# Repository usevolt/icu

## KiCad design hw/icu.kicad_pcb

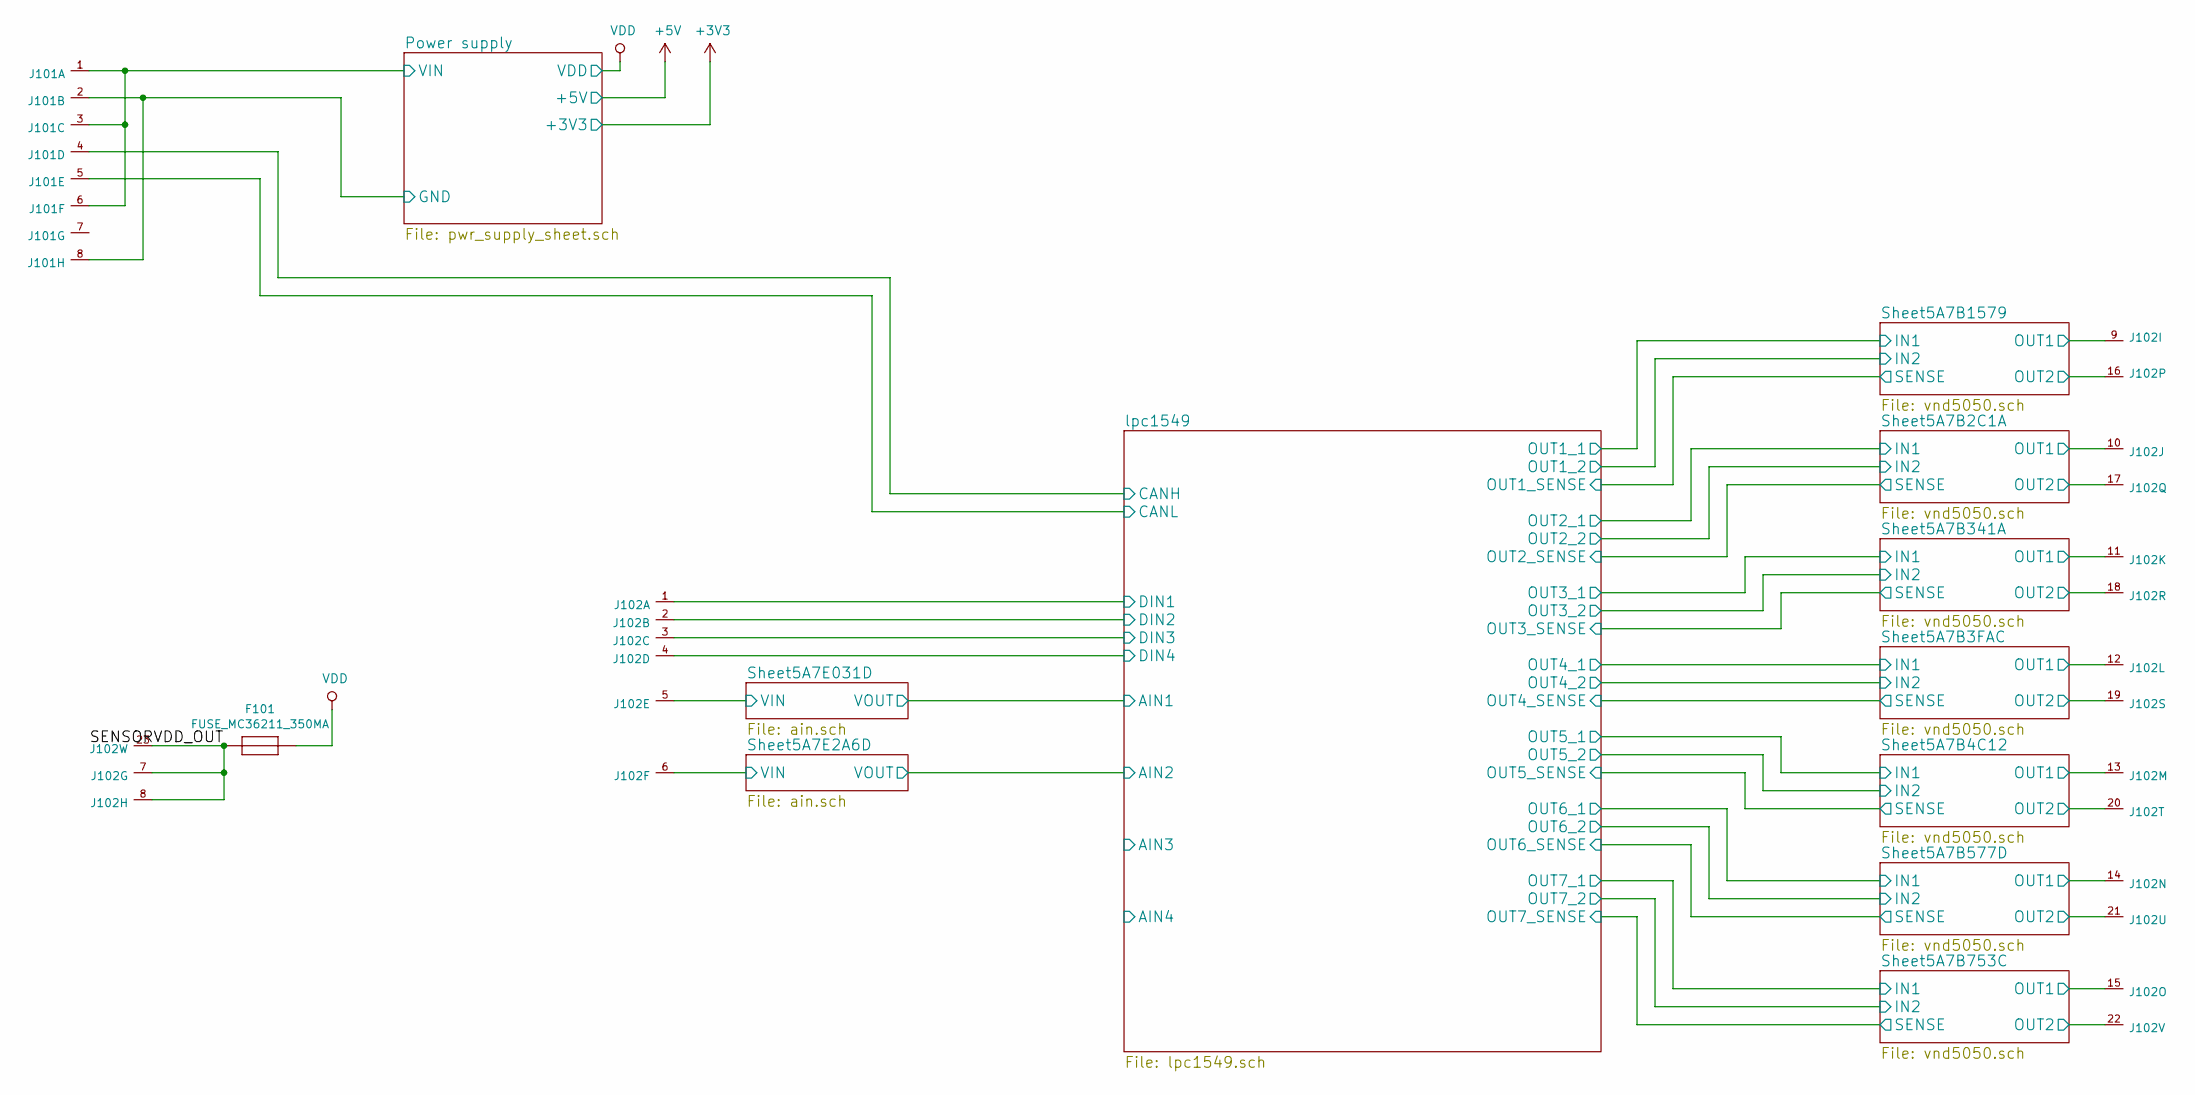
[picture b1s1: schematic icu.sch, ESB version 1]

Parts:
F101: FUSE_MC36211_350MA; FUSE_MC36211; Manufacturer Part Number MC36211
J101: AMPSEAL_8_POS_VERT_BLACK_SEALED_1-776276-1; AMPSEAL_8_POS_776275-1; Manufacturer Part Number 1-776276-1
J102: AMPSEAL_23_POS_VERT_GRAY_SEALED_1-776228-4; AMPSEAL_23_POS_776200-1; Manufacturer Part Number 1-776228-4

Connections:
/Power supply/VIN: J101.1, J101.3, J101.6; also elsewhere on the board
/SENSORVDD_OUT: F101.P$2, J102.7, J102.8, J102.23
/Sheet5A7B2C1A/OUT1: J102.10; also elsewhere on the board
/Sheet5A7B2C1A/OUT2: J102.17; also elsewhere on the board
/Sheet5A7B3FAC/OUT1: J102.12; also elsewhere on the board
/Sheet5A7B3FAC/OUT2: J102.19; also elsewhere on the board
/Sheet5A7B4C12/OUT1: J102.13; also elsewhere on the board
/Sheet5A7B4C12/OUT2: J102.20; also elsewhere on the board
/Sheet5A7B341A/OUT1: J102.11; also elsewhere on the board
/Sheet5A7B341A/OUT2: J102.18; also elsewhere on the board
/Sheet5A7B577D/OUT1: J102.14; also elsewhere on the board
/Sheet5A7B577D/OUT2: J102.21; also elsewhere on the board
/Sheet5A7B753C/OUT1: J102.15; also elsewhere on the board
/Sheet5A7B753C/OUT2: J102.22; also elsewhere on the board
/Sheet5A7B1579/OUT1: J102.9; also elsewhere on the board
/Sheet5A7B1579/OUT2: J102.16; also elsewhere on the board
/Sheet5A7E2A6D/VIN: J102.6; also elsewhere on the board
/Sheet5A7E031D/VIN: J102.5; also elsewhere on the board
/lpc1549/CANH: J101.4; also elsewhere on the board
/lpc1549/CANL: J101.5; also elsewhere on the board
/lpc1549/DIN1: J102.1; also elsewhere on the board
/lpc1549/DIN2: J102.2; also elsewhere on the board
/lpc1549/DIN3: J102.3; also elsewhere on the board
/lpc1549/DIN4: J102.4; also elsewhere on the board
GND: J101.2, J101.8; also elsewhere on the board
VDD: F101.P$1; also elsewhere on the board

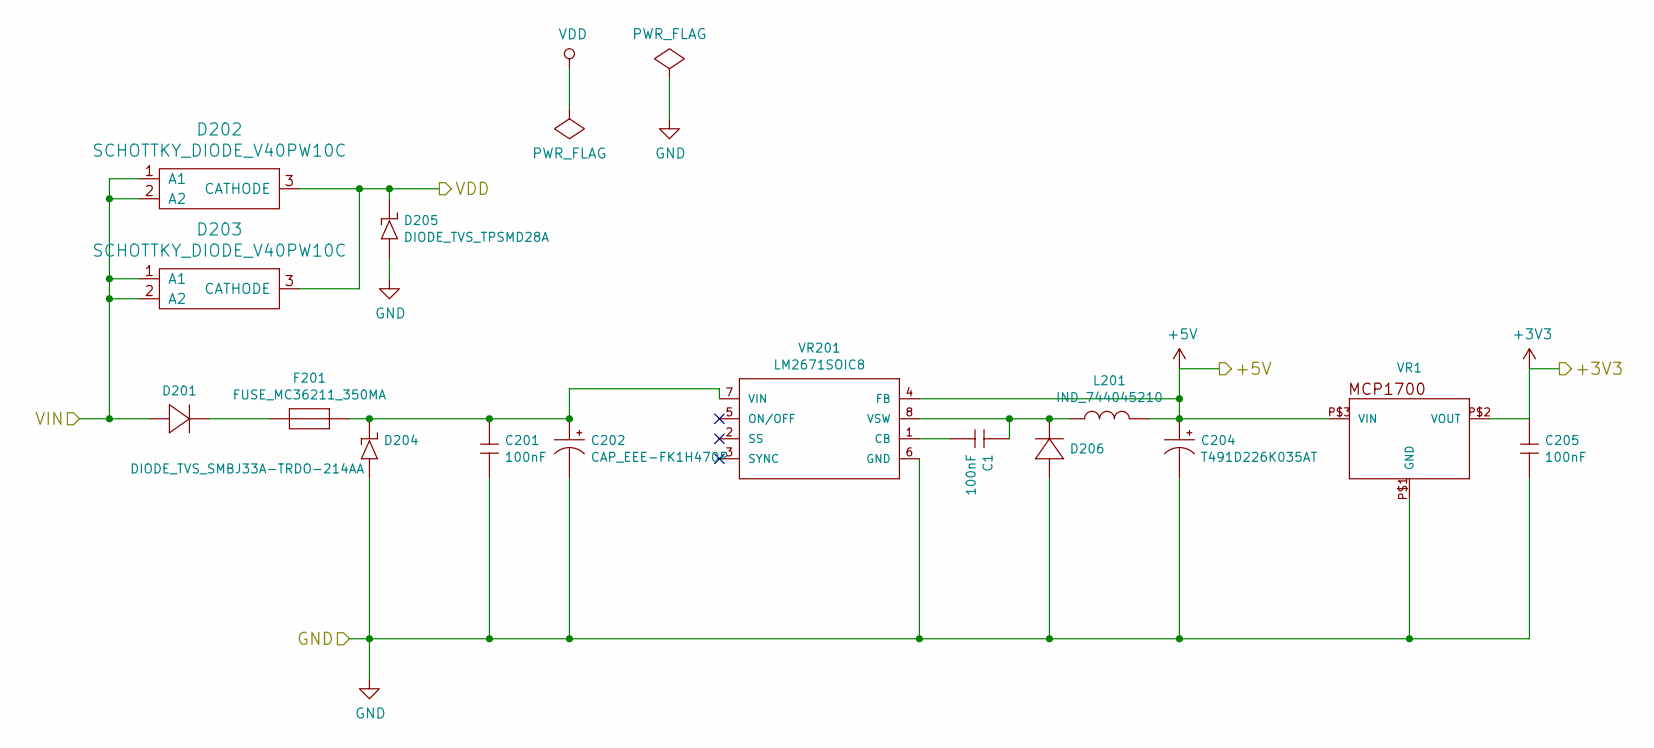
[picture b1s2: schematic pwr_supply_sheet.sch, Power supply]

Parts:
C1, C201, C205: 100nF; 0603; Manufacturer Part Number C0603C104K5RACTU
C202: CAP_EEE-FK1H470P; Manufacturer Part Number EEE-FK1H470P
C204: T491D226K035AT; 7343; Manufacturer Part Number T491D226K035AT
D201, D206: DIODE_RS07J-GS18; DO219AB; Manufacturer Part Number RS07J-GS18
D202, D203: SCHOTTKY_DIODE_V40PW10C; SlimDPAK; Manufacturer Part Number V40PW10CHM3/I
D204: DIODE_TVS_SMBJ33A-TRDO-214AA; DO-214AA; Manufacturer Part Number SMBJ33A
D205: DIODE_TVS_TPSMD28A; DO-214AB; Manufacturer Part Number TPSMD28A
F201: FUSE_MC36211_350MA; FUSE_MC36211; Manufacturer Part Number MC36211
L201: IND_744045210; Manufacturer Part Number 744045210
VR1: REG_MCP1700; SOT-23_3-PIN; Manufacturer Part Number MCP1700T-3302E/TT
VR201: LM2671SOIC8; SOIC8; Manufacturer Part Number LM2671M-5.0/NOPB

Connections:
+3V3: C205.1 (C1), VR1.2, VR1.P$2 (VOUT); also elsewhere on the board
+5V: C204.+, L201.2, VR1.3, VR1.P$3 (VIN), VR201.4 (FB); also elsewhere on the board
/Power supply/VIN: D201.P$1, D202.1 (A1), D202.2 (A2), D203.1 (A1), D203.2 (A2); also elsewhere on the board
GND: C201.2 (C2), C202.-, C204.-, C205.2 (C2), D204.P$1, D205.1, D206.P$1, VR1.1, VR1.P$1 (GND), VR201.6 (GND); also elsewhere on the board
unnamed: C1.1 (C1), D206.P$2 (N), L201.1, VR201.8 (VSW)
unnamed: C1.2 (C2), VR201.1 (CB)
unnamed: C201.1 (C1), C202.+, D204.P$2 (N), F201.P$2, VR201.7 (VIN)
unnamed: D201.P$2 (N), F201.P$1
VDD: D202.3 (CATHODE), D203.3 (CATHODE), D205.2 (N); also elsewhere on the board

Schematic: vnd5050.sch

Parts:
C301: 4.7uF; 0603; Manufacturer Part Number C0603C475K8PACTU
D5: ZENER_MM3Z3V6T1G; SOD-323; Manufacturer Part Number MM3Z3V6T1G
D302, D303: DIODE_RS07J-GS18; DO219AB; Manufacturer Part Number RS07J-GS18
R5, R301, R302: 1K; 0603; Manufacturer Part Number RC0603FR-071KL
U301: VND5050AJTR-E; PowerSSO-12; Manufacturer Part Number VND5050AJTR-E

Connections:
/Sheet5A7B1579/IN1: R301.2 (R2), U301.3 (IN1); also elsewhere on the board
/Sheet5A7B1579/IN2: R302.2 (R2), U301.2 (IN2); also elsewhere on the board
/Sheet5A7B1579/OUT1: D302.P$2 (N), U301.8 (OUT1), U301.9 (OUT1); also elsewhere on the board
/Sheet5A7B1579/OUT2: D303.P$2 (N), U301.10 (OUT2), U301.11 (OUT2); also elsewhere on the board
GND: C301.1 (C1), D5.2, D302.P$1, D303.P$1, R5.2 (R2), R301.1 (R1), R302.1 (R1), U301.1 (GND); also elsewhere on the board
VDD: U301.7 (VCC), U301.12 (VCC), U301.13 (VCC); also elsewhere on the board

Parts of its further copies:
C401, C501, C601, C701, C801, C901: 4.7uF; 0603; Manufacturer Part Number C0603C475K8PACTU
D1, D2, D3, D4, D6, D7: ZENER_MM3Z3V6T1G; SOD-323; Manufacturer Part Number MM3Z3V6T1G
D402, D403, D502, D503, D602, D603, D702, D703, D802, D803, D902, D903: DIODE_RS07J-GS18; DO219AB; Manufacturer Part Number RS07J-GS18
R1, R2, R3, R4, R6, R7, R401, R402, R501, R502, R601, R602, R701, R702, R801, R802, R901, R902: 1K; 0603; Manufacturer Part Number RC0603FR-071KL
U401, U501, U601, U701, U801, U901: VND5050AJTR-E; PowerSSO-12; Manufacturer Part Number VND5050AJTR-E

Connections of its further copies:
/Sheet5A7B2C1A/IN1: R401.2 (R2), U401.3 (IN1); also elsewhere on the board
/Sheet5A7B2C1A/IN2: R402.2 (R2), U401.2 (IN2); also elsewhere on the board
/Sheet5A7B2C1A/OUT1: D402.P$2 (N), U401.8 (OUT1), U401.9 (OUT1); also elsewhere on the board
/Sheet5A7B2C1A/OUT2: D403.P$2 (N), U401.10 (OUT2), U401.11 (OUT2); also elsewhere on the board
/Sheet5A7B3FAC/IN1: R601.2 (R2), U601.3 (IN1); also elsewhere on the board
/Sheet5A7B3FAC/IN2: R602.2 (R2), U601.2 (IN2); also elsewhere on the board
/Sheet5A7B3FAC/OUT1: D602.P$2 (N), U601.8 (OUT1), U601.9 (OUT1); also elsewhere on the board
/Sheet5A7B3FAC/OUT2: D603.P$2 (N), U601.10 (OUT2), U601.11 (OUT2); also elsewhere on the board
/Sheet5A7B4C12/IN1: R701.2 (R2), U701.3 (IN1); also elsewhere on the board
/Sheet5A7B4C12/IN2: R702.2 (R2), U701.2 (IN2); also elsewhere on the board
/Sheet5A7B4C12/OUT1: D702.P$2 (N), U701.8 (OUT1), U701.9 (OUT1); also elsewhere on the board
/Sheet5A7B4C12/OUT2: D703.P$2 (N), U701.10 (OUT2), U701.11 (OUT2); also elsewhere on the board
/Sheet5A7B341A/IN1: R501.2 (R2), U501.3 (IN1); also elsewhere on the board
/Sheet5A7B341A/IN2: R502.2 (R2), U501.2 (IN2); also elsewhere on the board
/Sheet5A7B341A/OUT1: D502.P$2 (N), U501.8 (OUT1), U501.9 (OUT1); also elsewhere on the board
/Sheet5A7B341A/OUT2: D503.P$2 (N), U501.10 (OUT2), U501.11 (OUT2); also elsewhere on the board
/Sheet5A7B577D/IN1: R801.2 (R2), U801.3 (IN1); also elsewhere on the board
/Sheet5A7B577D/IN2: R802.2 (R2), U801.2 (IN2); also elsewhere on the board
/Sheet5A7B577D/OUT1: D802.P$2 (N), U801.8 (OUT1), U801.9 (OUT1); also elsewhere on the board
/Sheet5A7B577D/OUT2: D803.P$2 (N), U801.10 (OUT2), U801.11 (OUT2); also elsewhere on the board
/Sheet5A7B753C/IN1: R901.2 (R2), U901.3 (IN1); also elsewhere on the board
/Sheet5A7B753C/IN2: R902.2 (R2), U901.2 (IN2); also elsewhere on the board
/Sheet5A7B753C/OUT1: D902.P$2 (N), U901.8 (OUT1), U901.9 (OUT1); also elsewhere on the board
/Sheet5A7B753C/OUT2: D903.P$2 (N), U901.10 (OUT2), U901.11 (OUT2); also elsewhere on the board
/lpc1549/OUT2_SENSE: C401.2 (C2), D1.1, R1.1 (R1), U401.4 (IS1), U401.5 (IS2); also elsewhere on the board
/lpc1549/OUT3_SENSE: C501.2 (C2), D2.1, R2.1 (R1), U501.4 (IS1), U501.5 (IS2); also elsewhere on the board
/lpc1549/OUT4_SENSE: C601.2 (C2), D3.1, R3.1 (R1), U601.4 (IS1), U601.5 (IS2); also elsewhere on the board
/lpc1549/OUT5_SENSE: C701.2 (C2), D4.1, R4.1 (R1), U701.4 (IS1), U701.5 (IS2); also elsewhere on the board
/lpc1549/OUT7_SENSE: C901.2 (C2), D6.1, R6.1 (R1), U901.4 (IS1), U901.5 (IS2); also elsewhere on the board
GND: C401.1 (C1), C501.1 (C1), C601.1 (C1), C701.1 (C1), C801.1 (C1), C901.1 (C1), D1.2, D2.2, D3.2, D4.2, D6.2, D7.2, D402.P$1, D403.P$1, D502.P$1, D503.P$1, D602.P$1, D603.P$1, D702.P$1, D703.P$1, D802.P$1, D803.P$1, D902.P$1, D903.P$1, R1.2 (R2), R2.2 (R2), R3.2 (R2), R4.2 (R2), R6.2 (R2), R7.2 (R2), R401.1 (R1), R402.1 (R1), R501.1 (R1), R502.1 (R1), R601.1 (R1), R602.1 (R1), R701.1 (R1), R702.1 (R1), R801.1 (R1), R802.1 (R1), R901.1 (R1), R902.1 (R1), U401.1 (GND), U501.1 (GND), U601.1 (GND), U701.1 (GND), U801.1 (GND), U901.1 (GND); also elsewhere on the board
VDD: U401.7 (VCC), U401.12 (VCC), U401.13 (VCC), U501.7 (VCC), U501.12 (VCC), U501.13 (VCC), U601.7 (VCC), U601.12 (VCC), U601.13 (VCC), U701.7 (VCC), U701.12 (VCC), U701.13 (VCC), U801.7 (VCC), U801.12 (VCC), U801.13 (VCC), U901.7 (VCC), U901.12 (VCC), U901.13 (VCC); also elsewhere on the board

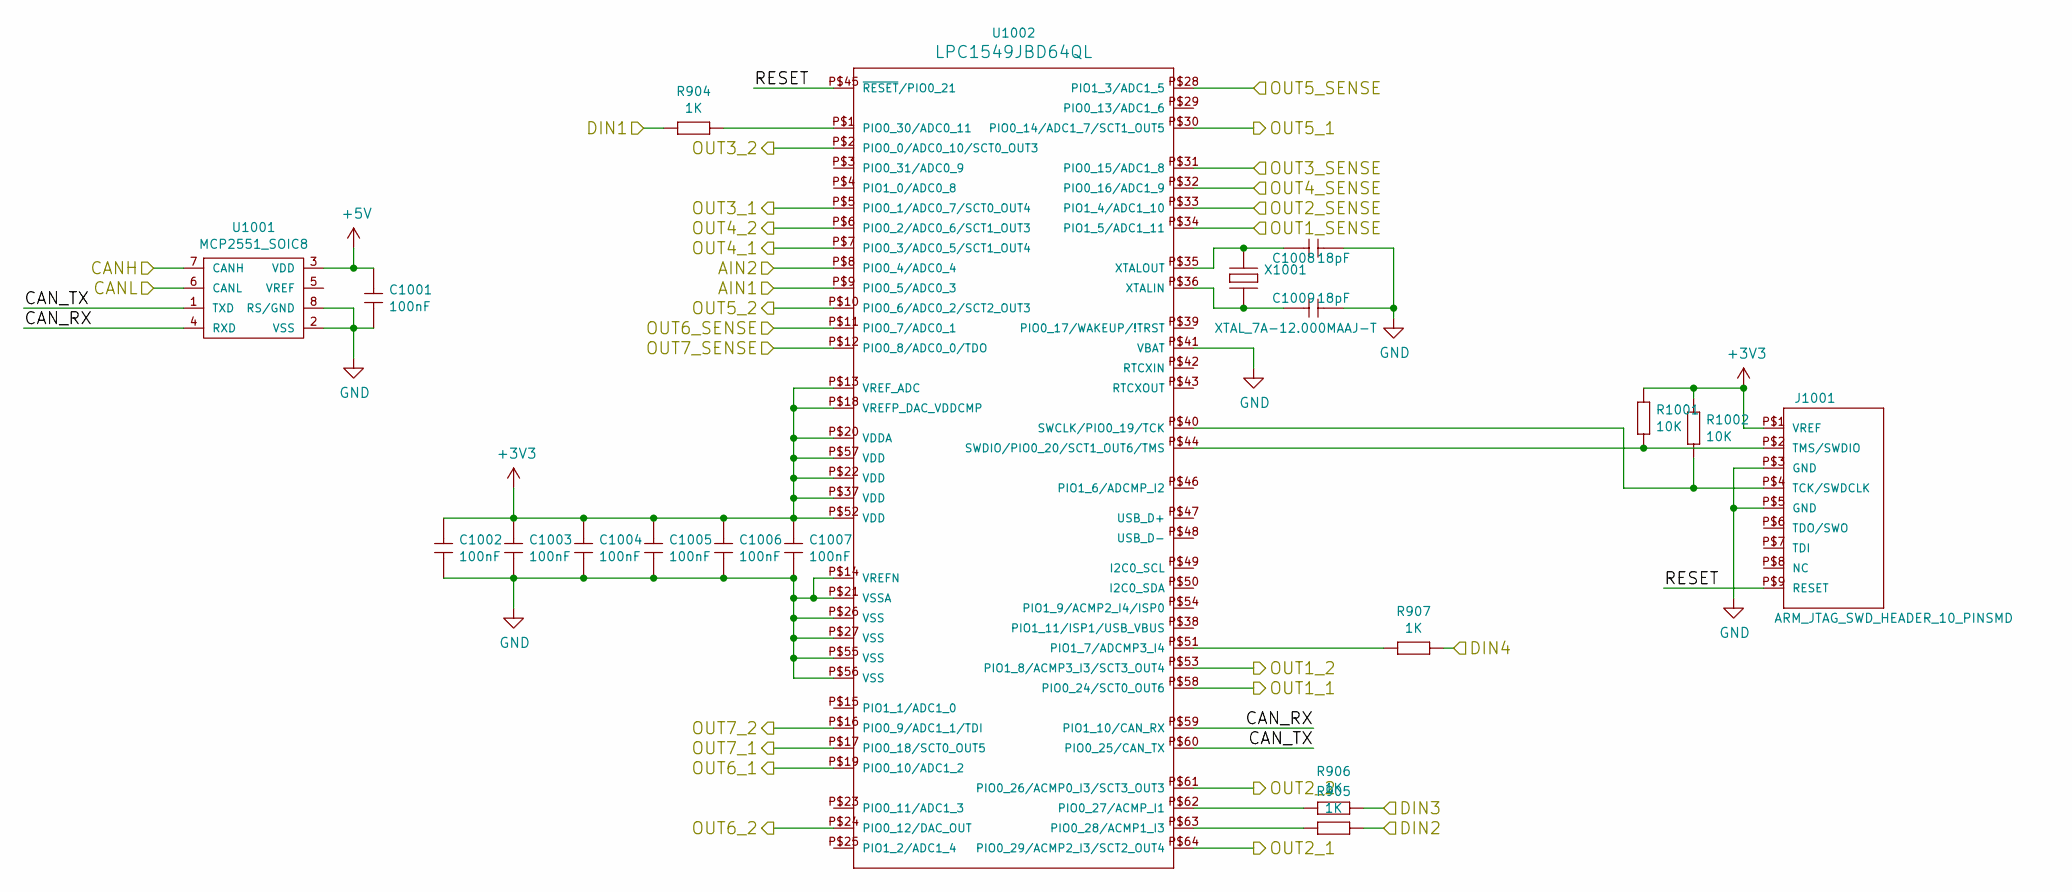
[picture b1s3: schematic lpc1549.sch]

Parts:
C1001, C1002, C1003, C1004, C1005, C1006, C1007: 100nF; 0603; Manufacturer Part Number C0603C104K5RACTU
C1008, C1009: 18pF; 0603; Manufacturer Part Number C0603C180J2GACTU
J1001: ARM_JTAG_SWD_HEADER_10_PINSMD; ARM_10_PIN_JTAG_SWD_CONNECTOR; Manufacturer Part Number 20021121-00010C4LF
R904, R905, R906, R907: 1K; 0603; Manufacturer Part Number RC0603FR-071KL
R1001, R1002: 10K; 0603; Manufacturer Part Number RC0603FR-0710KL
U1001: MCP2551_SOIC8; SOIC8; Manufacturer Part Number MCP2551-I/SN
U1002: LPC1549JBD64; QFP64; Manufacturer Part Number LPC1549JBD64QL
X1001: XTAL_7A-12.000MAAJ-T; XTAL_7A-20.000MAJ; Manufacturer Part Number 7A-12.000MAAJ-T

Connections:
+3V3: C1002.1 (C1), C1003.1 (C1), C1004.1 (C1), C1005.1 (C1), C1006.1 (C1), C1007.1 (C1), J1001.P$1 (VREF), R1001.2 (R2), R1002.2 (R2), U1002.P$13 (VREF_ADC), U1002.P$18 (VREFP_DAC_VDDCMP), U1002.P$20 (VDDA), U1002.P$22 (VDD), U1002.P$37 (VDD), U1002.P$52 (VDD), U1002.P$57 (VDD); also elsewhere on the board
+5V: C1001.1 (C1), U1001.3 (VDD); also elsewhere on the board
/Sheet5A7B2C1A/IN1: U1002.P$64 (PIO0_29/ACMP2_I3/SCT2_OUT4); also elsewhere on the board
/Sheet5A7B2C1A/IN2: U1002.P$61 (PIO0_26/ACMP0_I3/SCT3_OUT3); also elsewhere on the board
/Sheet5A7B3FAC/IN1: U1002.P$7 (PIO0_3/ADC0_5/SCT1_OUT4); also elsewhere on the board
/Sheet5A7B3FAC/IN2: U1002.P$6 (PIO0_2/ADC0_6/SCT1_OUT3); also elsewhere on the board
/Sheet5A7B4C12/IN1: U1002.P$30 (PIO0_14/ADC1_7/SCT1_OUT5); also elsewhere on the board
/Sheet5A7B4C12/IN2: U1002.P$10 (PIO0_6/ADC0_2/SCT2_OUT3); also elsewhere on the board
/Sheet5A7B341A/IN1: U1002.P$5 (PIO0_1/ADC0_7/SCT0_OUT4); also elsewhere on the board
/Sheet5A7B341A/IN2: U1002.P$2 (PIO0_0/ADC0_10/SCT0_OUT3); also elsewhere on the board
/Sheet5A7B577D/IN1: U1002.P$19 (PIO0_10/ADC1_2); also elsewhere on the board
/Sheet5A7B577D/IN2: U1002.P$24 (PIO0_12/DAC_OUT); also elsewhere on the board
/Sheet5A7B753C/IN1: U1002.P$17 (PIO0_18/SCT0_OUT5); also elsewhere on the board
/Sheet5A7B753C/IN2: U1002.P$16 (PIO0_9/ADC1_1/TDI); also elsewhere on the board
/Sheet5A7B1579/IN1: U1002.P$58 (PIO0_24/SCT0_OUT6); also elsewhere on the board
/Sheet5A7B1579/IN2: U1002.P$53 (PIO1_8/ACMP3_I3/SCT3_OUT4); also elsewhere on the board
/lpc1549/AIN1: U1002.P$9 (PIO0_5/ADC0_3); also elsewhere on the board
/lpc1549/AIN2: U1002.P$8 (PIO0_4/ADC0_4); also elsewhere on the board
/lpc1549/CANH: U1001.7 (CANH); also elsewhere on the board
/lpc1549/CANL: U1001.6 (CANL); also elsewhere on the board
/lpc1549/CAN_RX: U1001.4 (RXD), U1002.P$59 (PIO1_10/CAN_RX)
/lpc1549/CAN_TX: U1001.1 (TXD), U1002.P$60 (PIO0_25/CAN_TX)
/lpc1549/DIN1: R904.2 (R2); also elsewhere on the board
/lpc1549/DIN2: R905.2 (R2); also elsewhere on the board
/lpc1549/DIN3: R906.2 (R2); also elsewhere on the board
/lpc1549/DIN4: R907.1 (R1); also elsewhere on the board
/lpc1549/OUT2_SENSE: U1002.P$33 (PIO1_4/ADC1_10); also elsewhere on the board
/lpc1549/OUT3_SENSE: U1002.P$31 (PIO0_15/ADC1_8); also elsewhere on the board
/lpc1549/OUT4_SENSE: U1002.P$32 (PIO0_16/ADC1_9); also elsewhere on the board
/lpc1549/OUT5_SENSE: U1002.P$28 (PIO1_3/ADC1_5); also elsewhere on the board
/lpc1549/OUT7_SENSE: U1002.P$12 (PIO0_8/ADC0_0/TDO); also elsewhere on the board
/lpc1549/RESET: J1001.P$9 (RESET), U1002.P$45 (~RESET~/PIO0_21)
GND: C1001.2 (C2), C1002.2 (C2), C1003.2 (C2), C1004.2 (C2), C1005.2 (C2), C1006.2 (C2), C1007.2 (C2), C1008.2 (C2), C1009.2 (C2), J1001.P$3 (GND), J1001.P$5 (GND), U1001.2 (VSS), U1001.8 (RS/GND), U1002.P$14 (VREFN), U1002.P$21 (VSSA), U1002.P$26 (VSS), U1002.P$27 (VSS), U1002.P$41 (VBAT), U1002.P$55 (VSS), U1002.P$56 (VSS); also elsewhere on the board
unnamed: C1008.1 (C1), U1002.P$35 (XTALOUT), X1001.P$1
unnamed: C1009.1 (C1), U1002.P$36 (XTALIN), X1001.P$2
unnamed: J1001.P$2 (TMS/SWDIO), R1001.1 (R1), U1002.P$44 (SWDIO/PIO0_20/SCT1_OUT6/TMS)
unnamed: J1001.P$4 (TCK/SWDCLK), R1002.1 (R1), U1002.P$40 (SWCLK/PIO0_19/TCK)
unnamed: R904.1 (R1), U1002.P$1 (PIO0_30/ADC0_11)
unnamed: R905.1 (R1), U1002.P$63 (PIO0_28/ACMP1_I3)
unnamed: R906.1 (R1), U1002.P$62 (PIO0_27/ACMP_I1)
unnamed: R907.2 (R2), U1002.P$51 (PIO1_7/ADCMP3_I4)

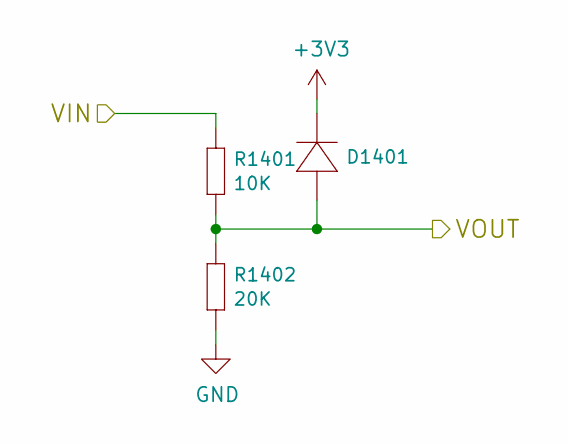
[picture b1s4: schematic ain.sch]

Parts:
D1101: DIODE_RS07J-GS18; DO219AB; Manufacturer Part Number RS07J-GS18
R1101: 10K; 0603; Manufacturer Part Number RC0603FR-0710KL
R1102: 20K; 0603; Manufacturer Part Number RC0603FR-0720KL

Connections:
+3V3: D1101.P$2 (N); also elsewhere on the board
/Sheet5A7E031D/VIN: R1101.2 (R2); also elsewhere on the board
/lpc1549/AIN1: D1101.P$1, R1101.1 (R1), R1102.2 (R2); also elsewhere on the board
GND: R1102.1 (R1); also elsewhere on the board

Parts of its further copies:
D1201, D1301, D1401: DIODE_RS07J-GS18; DO219AB; Manufacturer Part Number RS07J-GS18
R1201, R1301, R1401: 10K; 0603; Manufacturer Part Number RC0603FR-0710KL
R1202, R1302, R1402: 20K; 0603; Manufacturer Part Number RC0603FR-0720KL

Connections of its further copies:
+3V3: D1201.P$2 (N); also elsewhere on the board
/Sheet5A7E2A6D/VIN: R1201.2 (R2); also elsewhere on the board
/lpc1549/AIN2: D1201.P$1, R1201.1 (R1), R1202.2 (R2); also elsewhere on the board
GND: R1202.1 (R1); also elsewhere on the board

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
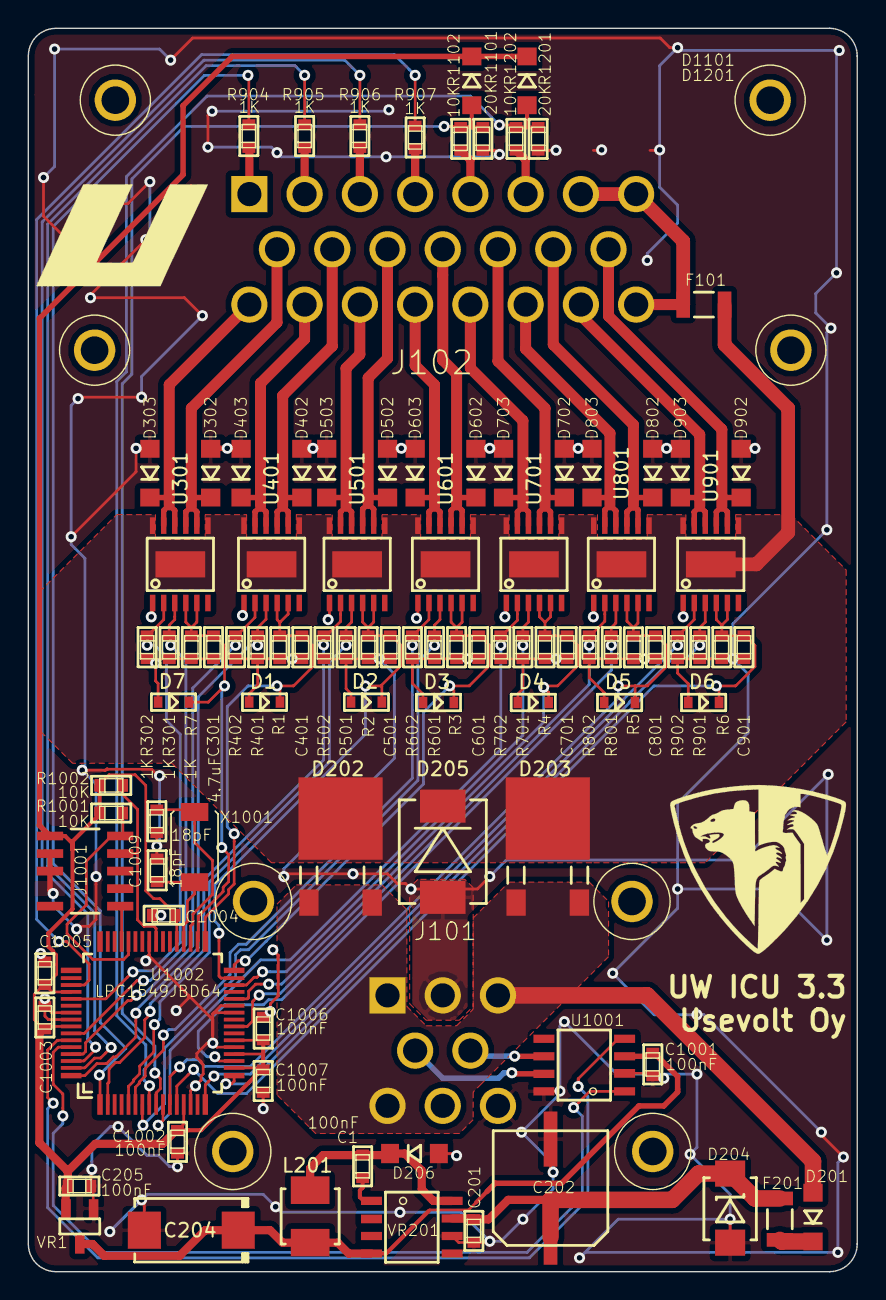
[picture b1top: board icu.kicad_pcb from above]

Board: 2 copper layers, 60.0 x 90.0 mm, 99 parts (0 on the bottom side), 66 nets.

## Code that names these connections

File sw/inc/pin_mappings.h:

/*
 * pin_mappings.h
 *
 *  Created on: Jan 27, 2015
 *      Author: usenius
 *
 *  Defines keypad pin mappings for different pcb revisions used
 */

#ifndef UW_MB_SRC_PIN_MAPPINGS_H_
#define UW_MB_SRC_PIN_MAPPINGS_H_

#include <uv_gpio.h>
#include <uv_timer.h>
#include <uv_adc.h>


// Analog inputs
#define OUT1_SENSE	ADC1_11
#define OUT2_SENSE	ADC1_10
#define OUT3_SENSE	ADC1_8
#define OUT4_SENSE	ADC1_9
#define OUT5_SENSE	ADC1_5
#define OUT6_SENSE	ADC0_1
#define OUT7_SENSE	ADC0_0

// Digital inputs
#define DIN1	P0_30
#define DIN2	P0_28
#define DIN3	P0_27
#define DIN4	P1_7
#define DIN5	P0_5
#define DIN6	P0_4
#define DIN7	P1_0
#define DIN8	P0_31

// Digital outputs
#define OUT1_A	P0_24
#define OUT1_B	P1_8
#define OUT2_A	P0_29
#define OUT2_B	P0_26
#define OUT3_A	P0_1
#define OUT3_B	P0_0
#define OUT4_A	P0_3
#define OUT4_B	P0_2
#define OUT5_A	P0_14
#define OUT5_B	P0_6
#define OUT6_A	P0_10
#define OUT6_B	P0_12
#define OUT7_A	P0_18
#define OUT7_B	P0_9


#define BLADES_OPEN_OUT		1
#define FEED_OPEN_OUT		2
#define TILT_OUT			0
#define FEED_SAW_OUT		3
#define SAW_MOVE_OUT		4
#define SAW_IN_DIR			DUAL_OUTPUT_NEG
#define SAW_OUT_DIR			DUAL_OUTPUT_POS
#define FEED_SERIES_DIR		DUAL_OUTPUT_NEG
#define SAW_DIR				DUAL_OUTPUT_POS



typedef struct {
	uv_adc_channels_e adc;
	uv_gpios_e gpioa;
	uv_gpios_e gpiob;
} out_st;

extern out_st outs[7];


#endif /* UW_MB_SRC_PIN_MAPPINGS_H_ */

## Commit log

2018-02-19 enclosure top & bottom ready to order
2018-02-20 hw 1.0 ready to order
2018-05-06 050518: Kikepera head prototype first revision, saw not working
2018-06-06 first working prototype in kikeperä
2018-06-09 analog inputs replaced with digital inputs
2018-07-07 pcb 2.0 created, with imu
2018-07-12 width measurement working
2018-08-10 implmenting different modules
2018-08-10 slowly getting moules working
2018-08-10 all modules working for first tim
2018-08-12 2 din replaced with ain, zeners added to outputs
2018-08-14 default values modified for feed finetune start
2018-09-07 implementing icu in CM_6.2.1
2018-09-09 CM_6.2.1 delivered, first customer machine with CCU, HCU & ICU
2018-09-13 feed target reaching bug fixes
2018-10-04 3.0.0 hw and gerber created
2018-10-04 hw 3.1 silkscreen modifications
2018-11-02 saw is pulled in for 100 ms when feeding stops
2018-11-13 CM_6.2.1 released, with volume measurement
2018-12-21 pcb 3.2.0 created, with 12V supply for sensors
2019-01-23 3.3 pcb created
2019-01-24 3.4.0 pcb created
2019-02-21 feed fuzzy controller values modified
2019-02-25 tilt float implemented
2019-05-10 blades & feed open bugfix:
    Delay in keeping the valve open after the request has stopped dos not cause a delay when changing the allopen direction
2019-05-22 feedclosing is disabled if feedopen_on_time is set to zero
2019-06-20 finetuned the feed length
2019-09-10 allopen operates tilt also, tilt mapped to right keypad button 7
2019-09-16 160919: testing feedclosing before starting moving tilt
2019-10-03 width meas default values added according to CM_6.3.2
2019-10-09 submodule urls set to https github
2019-10-10 vol measurement is added for all logs that have a positive length of 8cm or greater
2019-10-30 parallel feeding works also on all open
2019-11-02 021119: additional valve driving implemented for releasing pressure from the head when not used
2019-11-19 tiltonthumb parameter determines how tilt is controlled
2019-11-22 tilt float implemented#
2019-12-22 width measurement mad easier: only min_mm and max_mm are required
2020-01-09 bugfix: all_open saw uses saw settings for speed settings
2020-01-18 allopen tilt bugfix: uses tilt speed settings instead of saw
2020-04-29 small updates on schematic
2020-05-19 feed update: puts the feed to UNREACED mode if the target was passed
2020-07-21 feed logic modifid, should be able to feed backwards on auto feeding
2020-08-05 feed step params modified
2020-12-30 uw250 initial commit
2020-12-30 icu.json database addded
2021-01-02 feed len inc reduced greatly for separate length meas wheel
2021-01-04 tilt float doesnt go ON after sawing, feed target len def params fine tuned for uw250s
2021-04-24 feed continues
2022-04-19 kikepera icu forcepump added
